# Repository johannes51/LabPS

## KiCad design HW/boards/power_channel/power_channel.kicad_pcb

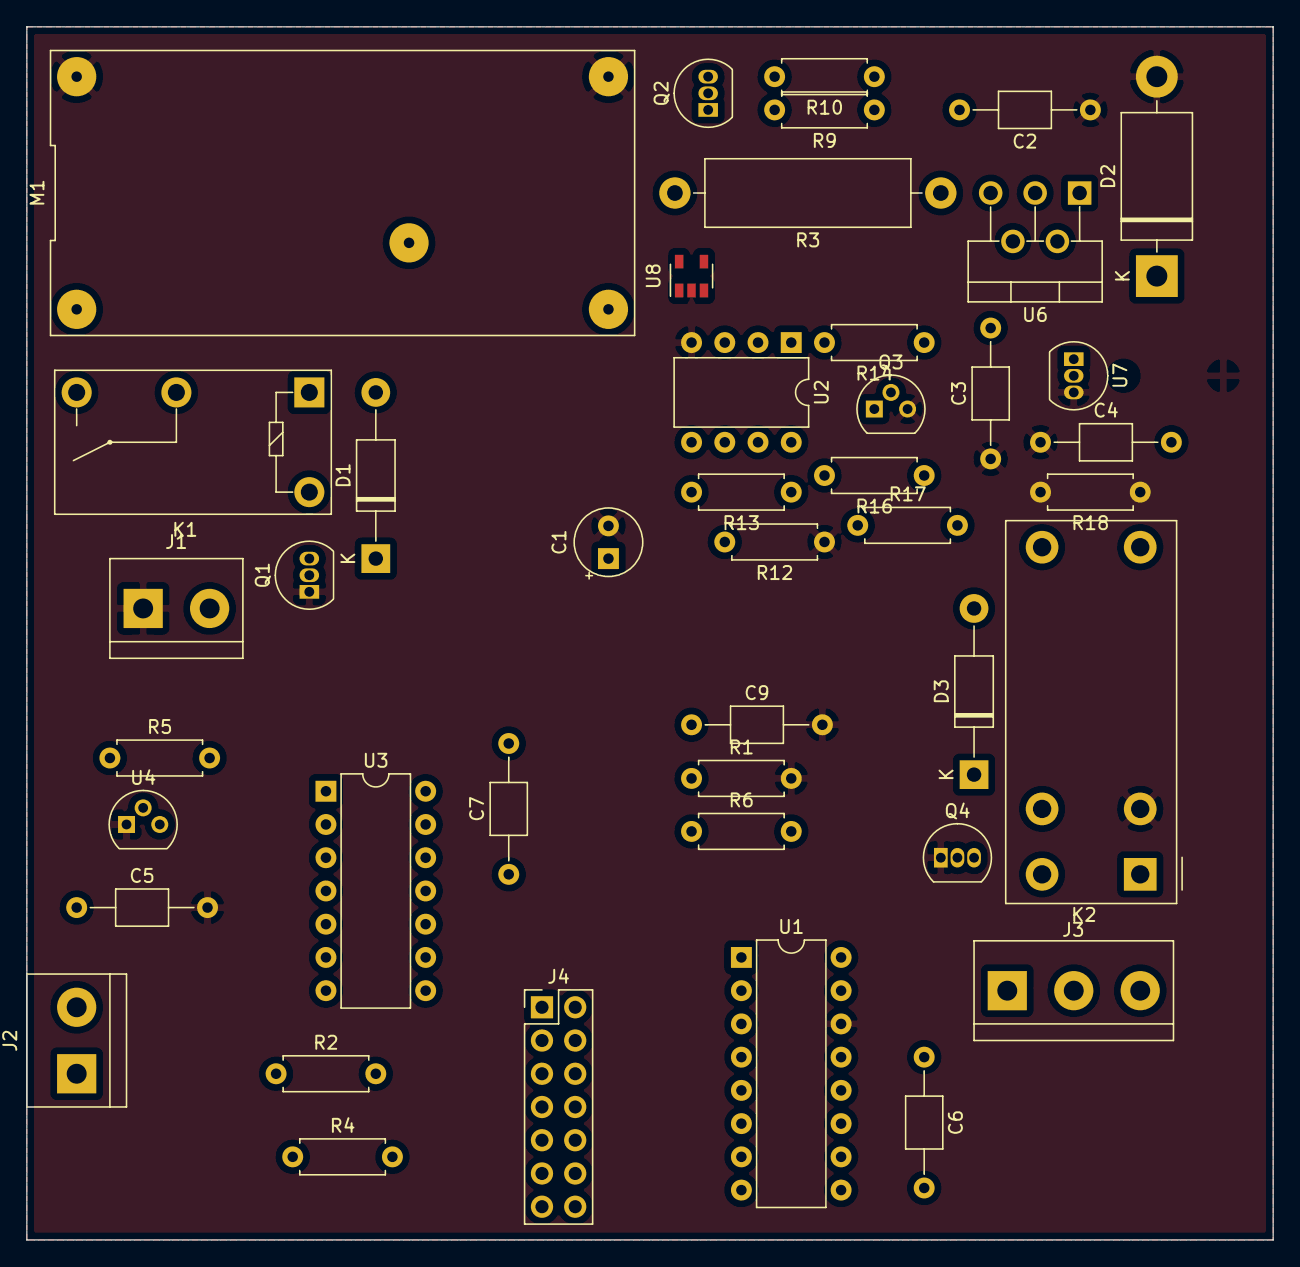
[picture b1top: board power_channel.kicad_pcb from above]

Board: 2 copper layers, 95.2 x 92.7 mm, 43 parts (0 on the bottom side), 43 nets, no tracks yet.

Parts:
C1: C; CP_Radial_Tantal_D5.0mm_P2.50mm
C2, C3, C4, C5, C6, C7, C9: C; C_Axial_L3.8mm_D2.6mm_P10.00mm_Horizontal
D1, D3: D; D_DO-41_SOD81_P12.70mm_Horizontal
D2: D_Schottky; D_DO-201AD_P15.24mm_Horizontal
J1, J2: Screw_Terminal_01x02; TerminalBlock_bornier-2_P5.08mm
J3: Screw_Terminal_01x03; TerminalBlock_bornier-3_P5.08mm
J4: Conn_02x07_Counter_Clockwise; PinHeader_2x07_P2.54mm_Vertical
K1: G5Q-1A; Relay_SPST_Omron-G5Q-1A
K2: Fujitsu_FTR-F1A; Relay_DPST_Fujitsu_FTR-F1A
M1: LM2596-Buck; Buck_Module
Q1, Q2, Q4: BC327; TO-92_Inline
Q3: Q_NPN_BCE; TO-92
R1, R2, R4, R5, R6: R; R_Axial_DIN0207_L6.3mm_D2.5mm_P7.62mm_Horizontal
R3: 0.1R; R_Axial_DIN0516_L15.5mm_D5.0mm_P20.32mm_Horizontal
R9: 10R; R_Axial_DIN0207_L6.3mm_D2.5mm_P7.62mm_Horizontal
R10: 65?R; R_Axial_DIN0207_L6.3mm_D2.5mm_P7.62mm_Horizontal
R12: 4k7R; R_Axial_DIN0207_L6.3mm_D2.5mm_P7.62mm_Horizontal
R13: 22kR; R_Axial_DIN0207_L6.3mm_D2.5mm_P7.62mm_Horizontal
R14, R16, R17: 10kR; R_Axial_DIN0207_L6.3mm_D2.5mm_P7.62mm_Horizontal
R18: 82R; R_Axial_DIN0207_L6.3mm_D2.5mm_P7.62mm_Horizontal
U1: MCP3208; DIP-16_W7.62mm
U2: LM358; DIP-8_W7.62mm
U3: MCP4922; DIP-14_W7.62mm
U4: LT1029; TO-92
U6: LT3080xT; TO-220-5_P3.4x3.7mm_StaggerOdd_Lead3.8mm_Vertical
U7: LM334Z; TO-92_Inline
U8: INA196; SOT-23-5

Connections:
+5V: C6.1, C7.2, J2.2, R2.2, R5.2, U1.16, U3.1
+15V: C1.1, D1.1, D3.1, J1.2, K1.2, K1.5, K2.4, U2.8, U6.4, U8.3
/ADC_CS: J4.3, U1.10
/CH2: J4.14, U1.3
/CH3: J4.13, U1.4
/CH4: J4.12, U1.5
/CH5: J4.11, U1.6
/CH6: J4.10, U1.7
/CH7: J4.9, U1.8
/CLK: J4.7, U1.13, U3.4
/DAC_CS: J4.4, U3.3
/ENABLE_IN: J4.1, Q1.2
/ENABLE_OUT: J4.2, Q4.2
/FB: M1.2, Q2.1
/I_Out: U1.2, U2.2, U8.1
/MISO: J4.5, U1.12
/MOSI: J4.6, U1.11, U3.5
/OUT+: J3.1, K2.8
/OUT-: J3.3, K2.1
/V_Out: C9.1, R1.1, R6.1, U1.1
/analog/I_Set: U2.3, U3.10
/analog/OUT: C4.2, D2.1, K2.7, R9.1, U6.3, U7.1
/analog/SENSE+: M1.3, R3.2, U8.4
/analog/SENSE-: C2.2, R3.1, R10.1, U6.5, U8.5
/analog/SET: C3.2, R13.1, R17.1, U6.2
/analog/V_Set: U2.5, U3.14
/digital/V_ref: C5.1, R5.1, U1.15, U3.11, U3.13, U4.2
GND: C1.2, C2.1, C3.1, C4.1, C5.2, C9.2, D2.2, J1.1, K2.2, M1.4, M1.5, Q1.1, Q3.3, Q4.1, R1.2, R12.1, R18.2, U1.14, U2.4, U4.1, U7.3, U8.2
GNDD: C6.2, C7.1, J2.1, R4.2, U1.9, U3.12
unnamed: D1.2, K1.1, Q1.3
unnamed: D3.2, K2.5, Q4.3
unnamed: J3.2, R6.2
unnamed: K1.3, M1.1
unnamed: Q2.2, R9.2
unnamed: Q2.3, R10.2
unnamed: Q3.1, R16.1, R17.2
unnamed: Q3.2, R14.1
unnamed: R2.1, U3.9
unnamed: R4.1, U3.8
unnamed: R12.2, R13.2, U2.6
unnamed: R14.2, U2.1
unnamed: R16.2, U2.7
unnamed: R18.1, U7.2

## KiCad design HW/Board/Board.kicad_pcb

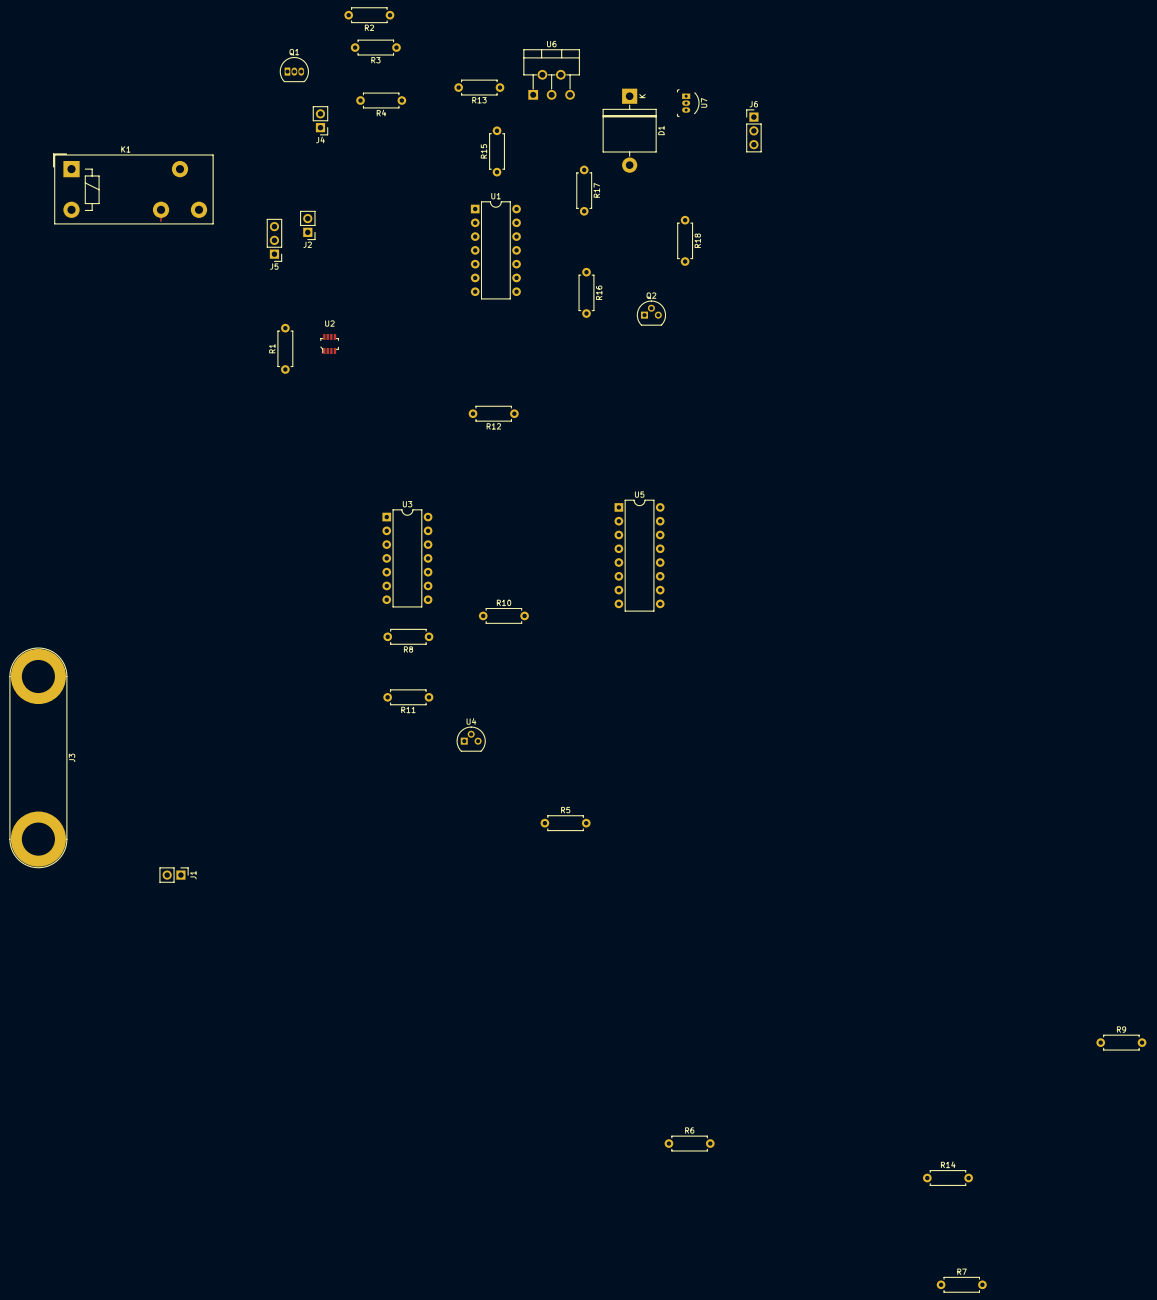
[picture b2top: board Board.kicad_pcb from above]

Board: 2 copper layers, 35 parts (0 on the bottom side), 33 nets.

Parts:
D1: D_Schottky; D_5KP_P12.70mm_Horizontal
J1, J2, J4: Screw_Terminal_01x02; PinHeader_1x02_P2.54mm_Vertical
J3: Barrel_Jack; Banana_Jack_2Pin
J5: Screw_Terminal_01x02; PinHeader_1x03_P2.54mm_Vertical
J6: Screw_Terminal_01x03; PinHeader_1x03_P2.54mm_Vertical
K1: FINDER-40.31; Relay_SPDT_Finder_40.31
Q1: BC327; TO-92_Inline
Q2: Q_NPN_BCE; TO-92
R1, R8, R10, R11: R; R_Axial_DIN0207_L6.3mm_D2.5mm_P7.62mm_Horizontal
R2: 10R; R_Axial_DIN0207_L6.3mm_D2.5mm_P7.62mm_Horizontal
R3: 65?R; R_Axial_DIN0207_L6.3mm_D2.5mm_P7.62mm_Horizontal
R4: 0.1R; R_Axial_DIN0207_L6.3mm_D2.5mm_P7.62mm_Horizontal
R5, R6: 1kR; R_Axial_DIN0207_L6.3mm_D2.5mm_P7.62mm_Horizontal
R7, R9: 8k2R; R_Axial_DIN0207_L6.3mm_D2.5mm_P7.62mm_Horizontal
R12: 4k7R; R_Axial_DIN0207_L6.3mm_D2.5mm_P7.62mm_Horizontal
R13: 22kR; R_Axial_DIN0207_L6.3mm_D2.5mm_P7.62mm_Horizontal
R14, R16, R17: 10kR; R_Axial_DIN0207_L6.3mm_D2.5mm_P7.62mm_Horizontal
R15: 530R; R_Axial_DIN0207_L6.3mm_D2.5mm_P7.62mm_Horizontal
R18: 82R; R_Axial_DIN0207_L6.3mm_D2.5mm_P7.62mm_Horizontal
U1: LM324; DIP-14_W7.62mm
U2: INA219AIDCNR; SOT-23-8
U3: MCP4922; DIP-14_W7.62mm
U4: LT1029; TO-92
U5: MCP3208; DIP-16_W7.62mm
U6: LT3080xT; TO-220-5_P3.4x3.7mm_StaggerOdd_Lead3.8mm_Vertical
U7: LM334Z_NOPB; TO-92-3

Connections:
+5V: J3.1, R8.2, R11.2, U2.4, U3.1, U5.16
+15V: J2.2, K1.11, U6.4
+VDC: J4.2, R4.2, R5.2, U1.4, U2.2
/Sheet5C1FCF32/CLK: J1.2, U3.4, U5.13
/Sheet5C1FCF32/I_Out: R9.1, U1.10, U1.14, U5.2
/Sheet5C1FCF32/I_Set: U1.9, U3.10
/Sheet5C1FCF32/MOSI: J1.1, U3.5, U5.11
/Sheet5C1FCF32/V_Out: J6.2, U5.1
/Sheet5C1FCF32/V_Set: U1.5, U3.14
/Sheet5C1FCF32/V_ref: R11.1, U3.11, U3.13, U4.2, U5.15
GND: D1.2, J2.1, J5.2, J6.3, Q2.3, R1.2, R7.1, R10.2, R12.1, R18.2, U2.3, U5.14, U7.3
GNDA: J4.1, U1.11
GNDD: J3.2, U3.12, U4.1, U5.9
unnamed: D1.1, J6.1, R2.1, U6.3, U7.1
unnamed: J5.1, K1.12
unnamed: J5.3, Q1.1
unnamed: Q1.2, R2.2
unnamed: Q1.3, R3.2
unnamed: Q2.1, R14.1
unnamed: Q2.2, R16.1, R17.2
unnamed: R1.1, U2.7, U2.8
unnamed: R3.1, R4.1, U1.3, U2.1, U6.5
unnamed: R5.1, R7.2, U1.12
unnamed: R6.1, R9.2, U1.13
unnamed: R6.2, U1.1, U1.2
unnamed: R8.1, U3.9
unnamed: R10.1, U3.8
unnamed: R12.2, R13.2, U1.6
unnamed: R13.1, R15.2
unnamed: R14.2, U1.8
unnamed: R15.1, R17.1, U6.2
unnamed: R16.2, U1.7
unnamed: R18.1, U7.2

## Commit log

2018-12-19 Settings, main-File
2018-12-19 Tests
2018-12-24 Changed structure, added Hardware
2019-08-25 wer weiß
2019-08-25 added documentation
2020-01-10 changed board around some, cleaned up libs
2020-01-10 changed folder structure, renamed project
2020-01-10 reworked power channel as board
2020-01-11 fertsch
2020-01-12 routed analog section
2020-01-20 reordered analog, started to internally connect digital
2020-01-24 found proper relays, deleted all traces to enable heatsink
2020-02-02 further refinement of schematic, rework opamp section then done
2020-02-04 schematic complete, placed power and analog components, preliminary placement of digital stuff, now route power
2021-11-14 whatever; final version
2022-07-12 small file mgmt, dunno
